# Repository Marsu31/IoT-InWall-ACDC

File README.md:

# IoT-InWall-ACDC

Ce montage est dérivé du projet [HLK-PM01 breakout board](https://www.openhardware.io/view/504/HLK-PM01-breakout-board). Ce dernier avait l'inconvénient de ne pas rentrer dans les boitiers muraux en France. J'ai donc décidé d'adapter l'implantation des composants.

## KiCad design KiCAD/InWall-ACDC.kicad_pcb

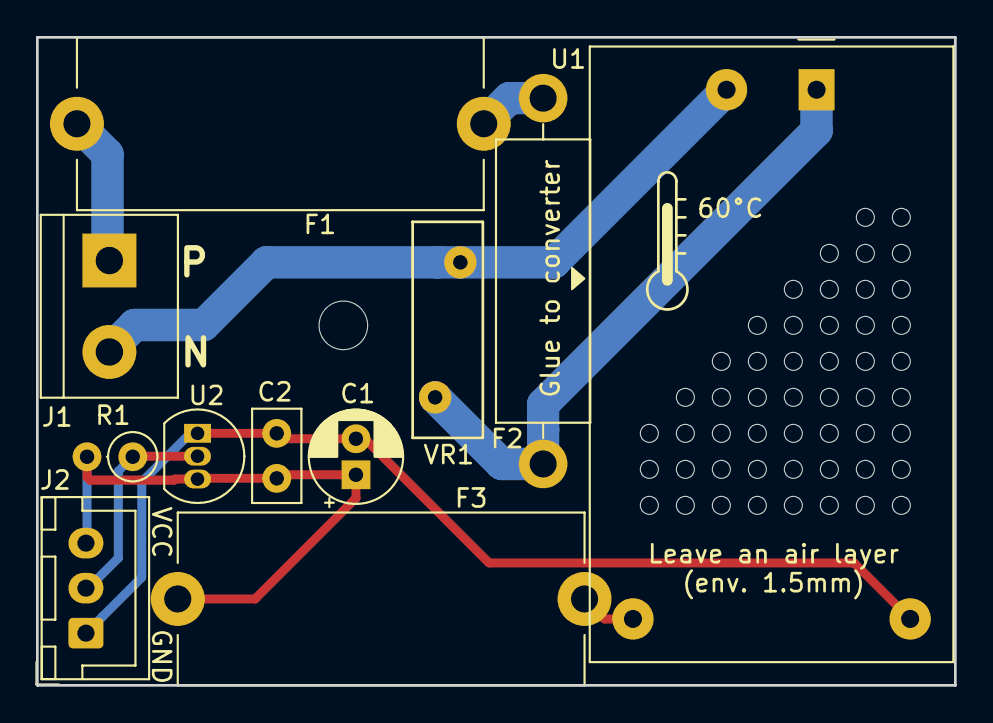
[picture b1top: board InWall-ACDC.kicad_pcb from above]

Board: 2 copper layers, 51.0 x 36.0 mm, 11 parts (0 on the bottom side), 8 nets.

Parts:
C1: 100u; CP_Radial_D5.0mm_P2.00mm
C2: 100n; C_Disc_D5.0mm_W2.5mm_P2.50mm
F1: slow blow (200mA); Fuseholder_Cylinder-5x20mm_Stelvio-Kontek_PTF78_Horizontal_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
F2: 73°C; R_Axial_DIN0516_L15.5mm_D5.0mm_P20.32mm_Horizontal
F3: fast blow (1A); Fuseholder_Cylinder-5x20mm_Stelvio-Kontek_PTF78_Horizontal_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
J1: Screw_Terminal_01x02; TerminalBlock_bornier-2_P5.08mm
J2: Conn_01x03; JST_XH_B3B-XH-A_1x03_P2.50mm_Vertical
R1: 4.7k; R_Axial_DIN0207_L6.3mm_D2.5mm_P2.54mm_Vertical
U1: HLK-PM03; Converter_ACDC_HiLink_HLK-PMxx
U2: DS18B20; TO-92_Inline
VR1: S10K275; RV_Disc_D12mm_W3.9mm_P7.5mm

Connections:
+3V3: C1.1, C2.1, F3.1, J2.3, R1.2, U2.3
GND: C1.2, C2.2, J2.1, U1.3, U2.1
LINE: F2.1, U1.1, VR1.1
NEUT: J1.2, U1.2, VR1.2
unnamed: F1.1, F2.2
unnamed: F1.2, J1.1
unnamed: F3.2, U1.4
unnamed: J2.2, R1.1, U2.2

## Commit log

2019-07-19 local lib: holes 0.5, 1mm
2019-07-20 logo
2019-07-20 allègement logo
2019-07-23 ajout modele 3D bornier + màj gerber
2024-05-12 commit de backup
